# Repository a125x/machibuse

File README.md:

# machibuse

Machibuse, 24-keys layout optimised for non-existent wrist movement and comfortable typing experience. Inspired by Colemac Mod-DH & Diktor layouts.

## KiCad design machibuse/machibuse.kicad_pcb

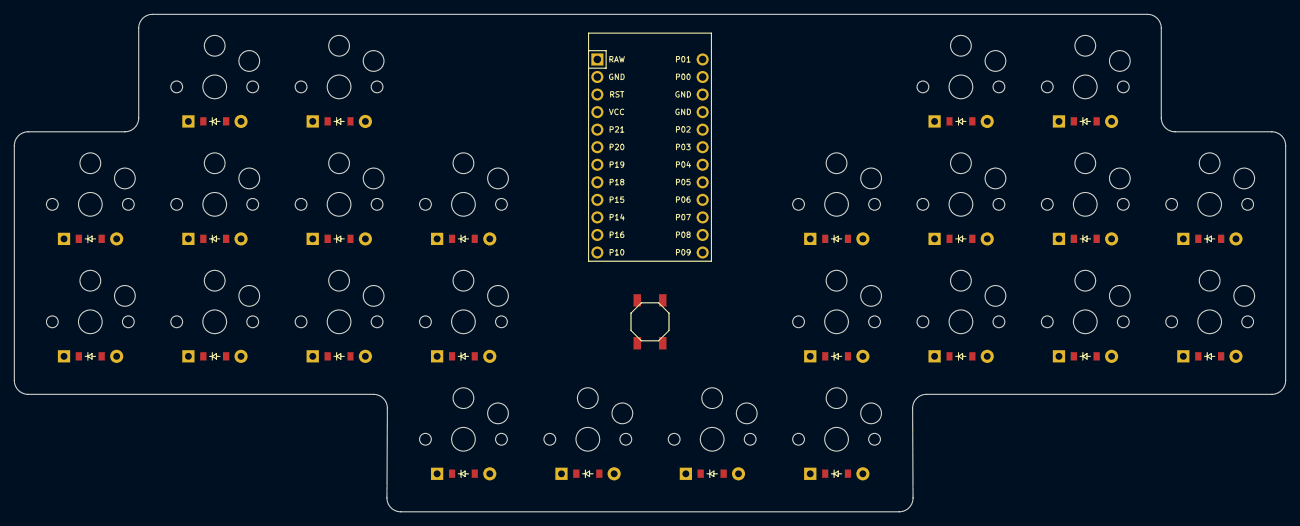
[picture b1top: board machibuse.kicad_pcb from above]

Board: 2 copper layers, 184.0 x 72.0 mm, 50 parts (0 on the bottom side), 26 nets, no tracks yet.

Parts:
B1: SW_TACT_ALPS_SKQGABE010
D1, D2, D3, D4, D5, D6, D7, D8, D9, D10, D11, D12, D13, D14, D15, D16, D17, D18, D19, D20, D21, D22, D23, D24: ComboDiode
MCU1: ProMicro
S1, S2, S3, S4, S5, S6, S7, S8, S9, S10, S11, S12, S13, S14, S15, S16, S17, S18, S19, S20, S21, S22, S23, S24: PG1350

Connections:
GND: B1.1, MCU1.2, MCU1.15, MCU1.16
RST: B1.2, MCU1.3
index_bottom: D9.2, S9.2
index_home: D10.2, S10.2
layer_cluster: D11.2, S11.2
middle_bottom: D6.2, S6.2
middle_home: D7.2, S7.2
middle_top: D8.2, S8.2
mirror_index_bottom: D21.2, S21.2
mirror_index_home: D22.2, S22.2
mirror_layer_cluster: D23.2, S23.2
mirror_middle_bottom: D18.2, S18.2
mirror_middle_home: D19.2, S19.2
mirror_middle_top: D20.2, S20.2
mirror_pinky_bottom: D13.2, S13.2
mirror_pinky_home: D14.2, S14.2
mirror_ring_bottom: D15.2, S15.2
mirror_ring_home: D16.2, S16.2
mirror_ring_top: D17.2, S17.2
mirror_space_cluster: D24.2, S24.2
pinky_bottom: D1.2, S1.2
pinky_home: D2.2, S2.2
ring_bottom: D3.2, S3.2
ring_home: D4.2, S4.2
ring_top: D5.2, S5.2
space_cluster: D12.2, S12.2

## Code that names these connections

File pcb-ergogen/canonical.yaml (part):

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    autobind: 10
    skip: false
    asym: both
    colrow: pinky_bottom
    name: board_pinky_bottom
    zone: &ref_1
      rows:
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    autobind: 10
    skip: false
    asym: both
    colrow: pinky_home
    name: board_pinky_home
    zone: *ref_1
    col: *ref_0
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    autobind: 10
    skip: false
    asym: both
    colrow: mirror_pinky_bottom
    name: mirror_board_pinky_bottom
    zone:
      rows:
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    autobind: 10
    skip: false
    asym: both
    colrow: mirror_pinky_home
    name: mirror_board_pinky_home
    zone:
      rows:
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
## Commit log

2023-02-12 init
2023-02-21 added a lot of tap dances
2023-02-25 added a lot of tap d
2023-02-25 made changing lahguage more convinient
2023-02-28 added combos and changed overall layout
2023-03-02 pre-update to the new firmware version
2023-03-06 removed useless functionality
2023-03-15 added ergogen
2023-03-16 made file structure more understandable
2023-03-18 used quantum instead of tap dance for home row mode
2023-03-19 added mouse support for a russian layers
2023-04-03 created kinda great keymap finally, removed useless combos
2023-04-30 changed default backspace to option+backspace
2023-05-01 added shortcuts to open applications easily
2023-05-04 added alt+arrows to move around words more quickly
2023-05-05 added kawa so changing input methond is much less frustrating
2023-05-06 redused usage of macros by swapping them to quantum
2023-05-09 changed position of some keys to make layout more usable and ergonomic
2023-05-11 added proper macros to make a window screenshot in one tap
2023-05-26 added f row
2023-06-21 removed layer duplicates and added home row mode to almost all the layers
2023-06-27 added more macros for <, > and {}. Deleted single alt tab
2023-06-27 added warning
2023-07-10 changed reset
2023-07-20 moved screenshots a bit further away to prevent mistakes and made : and ; punktuation more accessible on russian
2023-07-25 fixed home row on the first layer positioning
2023-07-28 in the process of creating pcb for machibuse keyboard
2023-08-05 replaced opt+backspace to the usual backspace. In the ideal world Id like to use opt+del as the main way to delete things, but honestly del have kinda the same usability in usual typint and better su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
2023-08-09 simplified keyboard layout by removing a lot of tap dances. It become possible by using full power of home row mods. Also embedded shortcuts arent available in every application so it make sense to u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
2023-08-09 removed previous versions (why did i even kept em?)
2023-08-09 brought back mouse layer, this time on the left hand. Idk will I really use it that often but still pretty cool thing to have.
2023-08-13 added pcb (unfinished)
2023-09-14 solved some issues with macros hopefully by not using them almost any fucking time. its so annoying to reattach keeb every few minutes and thinking about breaking anything,but i hope now there will b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
2023-09-15 honey new layout version just dropped
2023-09-24 added the last config for ergohaven before selling
2023-11-02 finally created layout for corne in qmk configurator
2023-11-04 fixed minor issues like scrollwill and home row modes
2023-11-04 added equialent of the russian layers filled with smth.. aah its unexplainable
2023-11-09 added russian language on the universal layout
2023-11-16 got everything possible from a simple qmk json configurer
2023-11-20 restructured file structure a bit
2023-11-24 added pdf version of the current layout generated by qmk configurator
2024-04-21 switched from json to c
2024-04-21 renamed machibuse
2024-05-06 Create LICENSE
2024-05-13 now macros for changing languages with one press of a button should work; cant test in now though
2024-05-17 added macros for brightness on shift of volume
